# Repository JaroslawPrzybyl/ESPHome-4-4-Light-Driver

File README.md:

# ESPHome-4-4-Light-Driver
**Small light controller with 4 AC SSR outputs and 4 optoisolated inputs, designed for Home Assistant.**

## Design
Not so much to describe - just ESP with power supply and I2C expander, where four ports are used as inputs and four as outputs. Design of inputs and outputs was using by me from a years with other Home Automation systems (old stuff based on AVR CPUs, currently swapping by a bit more modern, HomeAssistant compatible devices), without any problems.  
Outputs are made as SSR relays, switched with zero-cross detection. It means safe switching of any active  load like lamps, etc, but reactive load is not allowed here, so please don't use this device with any induction load, like e.g. engines.   
Inputs are designed for use momentary buttons, each input port responds to shorting it with the COM. Needed wiring of inputs (and outputs) is shown on schematic diagram, with grey lines.  

**WARNING! Don't connect input lines with AC installation or any external power lines, it must be fully separated, only direct connections to switch buttons are allowed**   

## Parts and components
Base of this device is an ESP-07 module, choosen due to possibility to connect external antenna. If it is not needed, can be used also ESP12 or any other with the same footprint, such change has be included in the code.
All other components are listed in BoM file.   

Connection between boards can be done by any method, pins have to be connected 1:1.   
Because reverse connection will damage ESP module, I would recommend to use any connection method, which avoid of it. Connector like  Molex KK would be the best solution, any other with raster 2,54 will be also ok. On my prototype I used ordinary goldpin connector with one pin more than needed, this pin is removed and corresponding pin in the plug is blinded by glue.

PSU: popular chinese HLK-PM01, 5V/0.6A. AC input is protected by varistor and 4A fuse. Due to lack of space I used small fuse SMD 1808 which is not recommended to use with voltage higher than 127V - I know, but I ignored it, because this part really suited me and here important for me was to have something able to make a break in the circuit. Load will be (should be!) active, so there shouldn't be a problems with overvoltage, arcs etc. Fuse is changeable, fuses and sockets were bought on Aliexpress:

https://www.aliexpress.com/item/32840204422.html

Terminal ports - I used old spare, which I had in my draver, but any with raster 5.08mm can be used here. Or - if needed, popular "green" sepparable Phoenix terminal blocks should fit here also.

## Assembly

PCB Gerber files are attached. It is not exactly the same version as shown on photos, it was a prototype, after I did some cosmetic corrections and here I put a final version.  
Both PCBs are prepared for standard DIN rail box case Gainta D3MG http://www.gainta.com/en/d3mg.html, nothing more is needed for assembly, both PCBs fit into the latches inside the case.    
External antena is optional, you can use it or stay with internal - up to you. When device is mounted inside of metal switchbox, external antenna mounted outside of box is strongly recommended.  
Stickers should be printed on self-adhesive paper or foil. In my projects I'm using self-adhesive printable white or silver foil, special for laser printers.   

## Software

From ESP-Home perspective it is really simple device, shouldn't be any problems with the code. The only important thing which should be pointed out is that when you use ESP-07, its integration in ESPHome contains a bug, which is not corrected from the years (was reported many times as I know, without any result). So in declaration of board type, instead of esp_07, has to be used esp01_1m and with this workaround everything works fine.  
Basic proposal of code is added into the files, each input controls its corresponding output, where "short" click on the button just switch on or off the output, "long" click (press and hold more than 1s) switches off all outputs (really useful option for fast switching off the lights in the room). Clicks shorter than 50ms are ignored (debouncing), longer than 5s are also ignored (could be additionally reported as a short circuit on the line, it is not included in this code, but can be simply done).   
Only line 4 works a bit different, here is implemented a timer: short click switches on Out4  for 30 seconds (time value is set as at the top of code), after this time output  will be switched off. Each time it can be switched off manually by click the button again. And long click here works differently: it switches on the output permanently (until switching off by pressing button). 

Exemplary entity works with this code (entity code added into files):

##  

Shield: [![CC BY-NC-SA 4.0][cc-by-nc-sa-shield]][cc-by-nc-sa]

This work is licensed under a
[Creative Commons Attribution-NonCommercial-ShareAlike 4.0 International License][cc-by-nc-sa].

[![CC BY-NC-SA 4.0][cc-by-nc-sa-image]][cc-by-nc-sa]

[cc-by-nc-sa]: http://creativecommons.org/licenses/by-nc-sa/4.0/
[cc-by-nc-sa-image]: https://licensebuttons.net/l/by-nc-sa/4.0/88x31.png
[cc-by-nc-sa-shield]: https://img.shields.io/badge/License-CC%20BY--NC--SA%204.0-lightgrey.svg

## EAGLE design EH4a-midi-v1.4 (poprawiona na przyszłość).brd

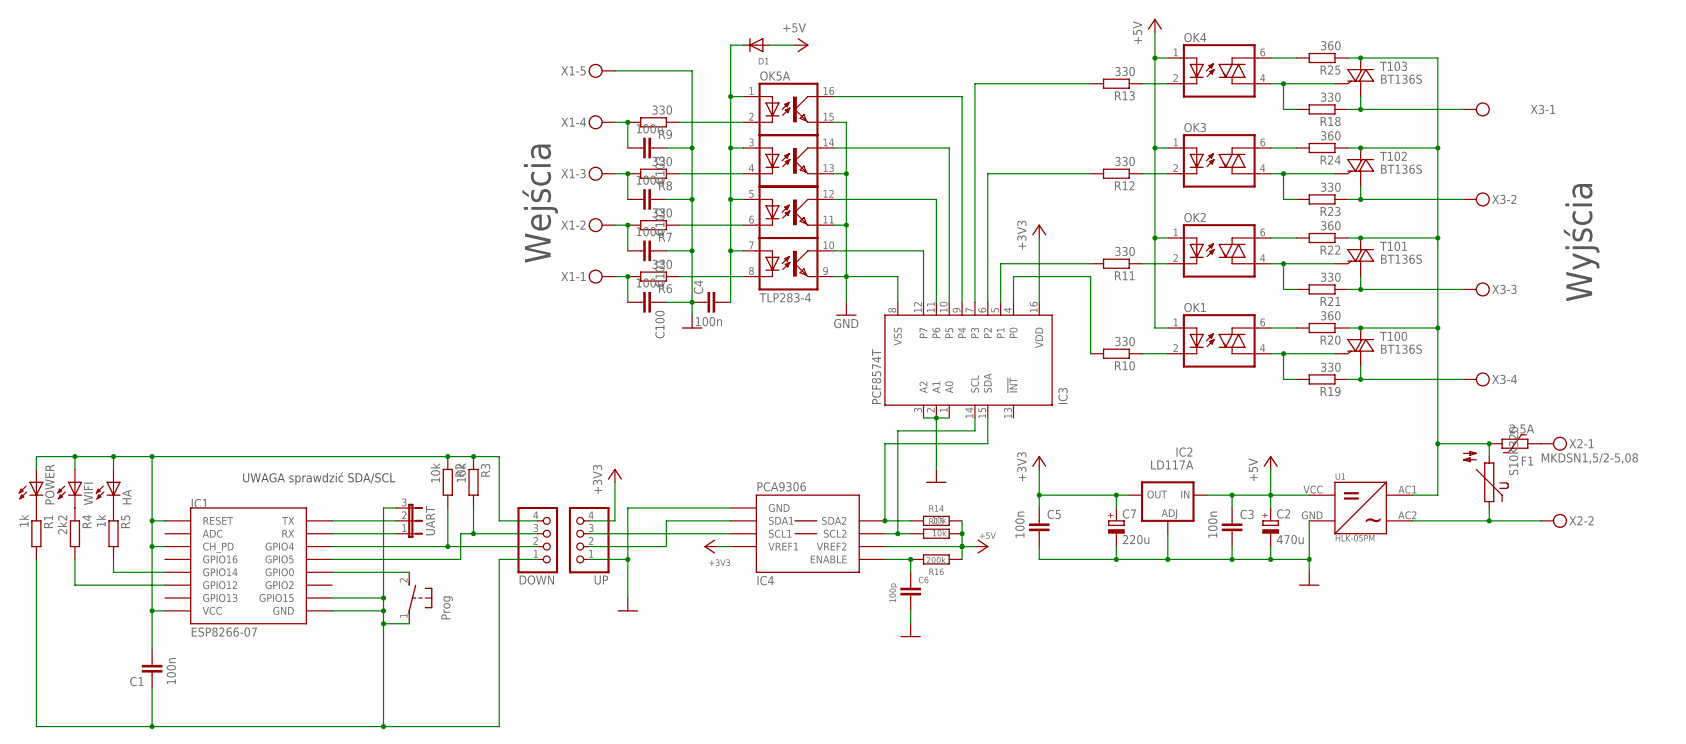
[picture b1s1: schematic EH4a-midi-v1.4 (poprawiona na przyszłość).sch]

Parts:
C1, C3, C4, C5, C100, C101, C102, C103: 100n; C0805
C2: 470u; E3,5-8
C6: 100p; C0805
C7: 220u; E2,5-7
D1: 1N4148; SOD-123
DOWN: PINHD-1X4; 1X04
F1: 2.5A; 2920L
HA: LED3MM
IC1: ESP8266-07; ESP12
IC2: LD117A; SOT223
IC3: PCF8574T; SO16W
IC4: PCA9306; MSOP08
OK1: MOC3043; DIL06
OK2, OK3, OK4: IL420; DIL06
OK5: TLP283-4; MINI-FLAT-16
POWER: LED3MM
R1, R5: 1k; M0805
R2, R3: 10k; M0805
R4: 2k2; M0805
R6, R7, R8, R9, R10, R11, R12, R13: 330; M0805
R14, R15: 10k; R0805
R16: 200k; R0805
R17: S10K320
R18, R19, R21, R23: 330; R1210
R20, R22, R24, R25: 360; R1210
S1: Prog; DTSM-3
T100, T101, T102, T103: BT136S; SOT428
U1: HLK-05PM; HLK-PM01_HLK-PM01
UART: JP2E; JP2
UP: PINHD-1X4; 1X04
WIFI: LED3MM
X1: MKDSN1,5/5-5,08
X2: MKDSN1,5/2-5,08
X3: MKDSN1,5/4-5,08

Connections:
3V3: C1.2, DOWN.4, HA.A, IC1.CH_PD, IC1.RESET, IC1.VCC, POWER.A, R2.1, R3.1, WIFI.A
+3V3: C5.1, C7.+, IC2.2 (OUT), IC2.4 (OUT), IC3.16 (VDD), IC4.2 (VREF1), UP.4
+5V: C2.+, C3.1, D1.A, IC2.3 (IN), IC4.7 (VREF2), OK1.1 (A), OK2.1 (A), OK3.1 (A), OK4.1 (A), R14.1, R15.1, R16.2, U1.VCC
GND: C2.-, C3.2, C4.1, C5.2, C6.2, C7.-, C100.1, C101.1, C102.1, C103.1, IC2.1 (ADJ), IC3.1 (A0), IC3.2 (A1), IC3.3 (A2), IC3.8 (VSS), IC4.1 (GND), OK5.9 (EMIT), OK5.11 (EMIT), OK5.13 (EMIT), OK5.15 (EMIT), U1.GND, UP.1, X1.5
GND1: C1.1, DOWN.1, IC1.GND, IC1.GPIO15, R1.2, S1.1, UART.3
L: F1.1, R17.2, R20.1, R22.1, R24.1, R25.1, T100.MB (LD), T101.MB (LD), T102.MB (LD), T103.MB (LD), U1.AC1
unnamed: IC3.7 (P3), R13.2
unnamed: IC3.10 (P5), OK5.14 (COL)
unnamed: IC3.11 (P6), OK5.12 (COL)
unnamed: IC3.12 (P7), OK5.10 (COL)
unnamed: IC3.6 (P2), R12.2
unnamed: OK4.2 (C), R13.1
unnamed: OK1.2 (C), R10.1
unnamed: OK2.2 (C), R11.1
unnamed: IC3.5 (P1), R11.2
unnamed: IC3.4 (P0), R10.2
unnamed: IC1.GPIO14, R5.2
unnamed: R17.1, U1.AC2, X2.2
unnamed: C103.2, R9.2, X1.4
unnamed: C102.2, R8.2, X1.3
unnamed: F1.2, X2.1
unnamed: POWER.K (C), R1.1
unnamed: R4.1, WIFI.K (C)
unnamed: HA.K (C), R5.1
unnamed: IC1.GPIO12, R4.2
unnamed: IC1.GPIO0, S1.2
unnamed: IC1.RX, UART.1
unnamed: IC1.TX, UART.2
unnamed: C6.1, IC4.8 (ENABLE), R16.1
unnamed: IC3.9 (P4), OK5.16 (COL)
unnamed: OK3.2 (C), R12.1
unnamed: C4.2, D1.C, OK5.1 (A), OK5.3 (A), OK5.5 (A), OK5.7 (A)
unnamed: OK5.2 (C), R9.1
unnamed: OK5.4 (C), R8.1
unnamed: OK5.6 (C), R7.1
unnamed: OK5.8 (C), R6.1
unnamed: OK1.4 (A1), R19.2, T100.3 (G)
unnamed: R19.1, T100.1 (CM), X3.4
unnamed: C101.2, R7.2, X1.2
unnamed: C100.2, R6.2, X1.1
unnamed: OK2.4 (A1), R21.2, T101.3 (G)
unnamed: R21.1, T101.1 (CM), X3.3
unnamed: OK3.4 (A1), R23.2, T102.3 (G)
unnamed: R23.1, T102.1 (CM), X3.2
unnamed: OK4.4 (A1), R18.2, T103.3 (G)
unnamed: R18.1, T103.1 (CM), X3.1
unnamed: OK4.6 (A2), R25.2
unnamed: OK3.6 (A2), R24.2
unnamed: OK2.6 (A2), R22.2
unnamed: OK1.6 (A2), R20.2
SCL: IC3.14 (SCL), IC4.6 (SCL2), R15.2
SCL1: DOWN.3, IC1.GPIO5, R3.2
SCL': IC4.3 (SCL1), UP.3
SDA: IC3.15 (SDA), IC4.5 (SDA2), R14.2
SDA1: DOWN.2, IC1.GPIO4, R2.2
SDA': IC4.4 (SDA1), UP.2

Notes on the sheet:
Wejścia
Wyjścia
UWAGA sprawdzić SDA/SCL

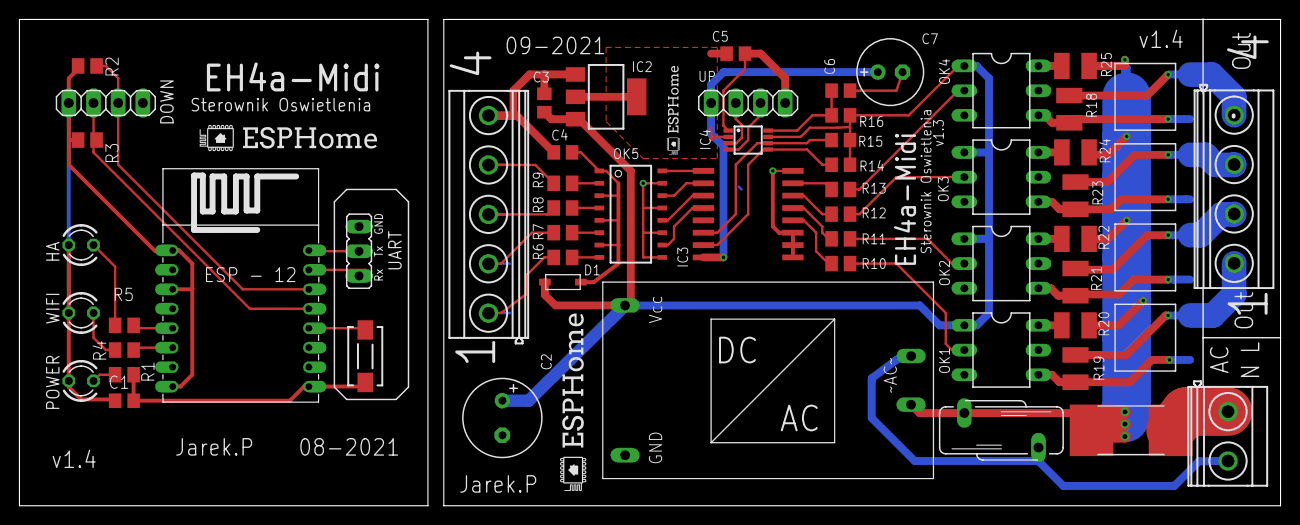
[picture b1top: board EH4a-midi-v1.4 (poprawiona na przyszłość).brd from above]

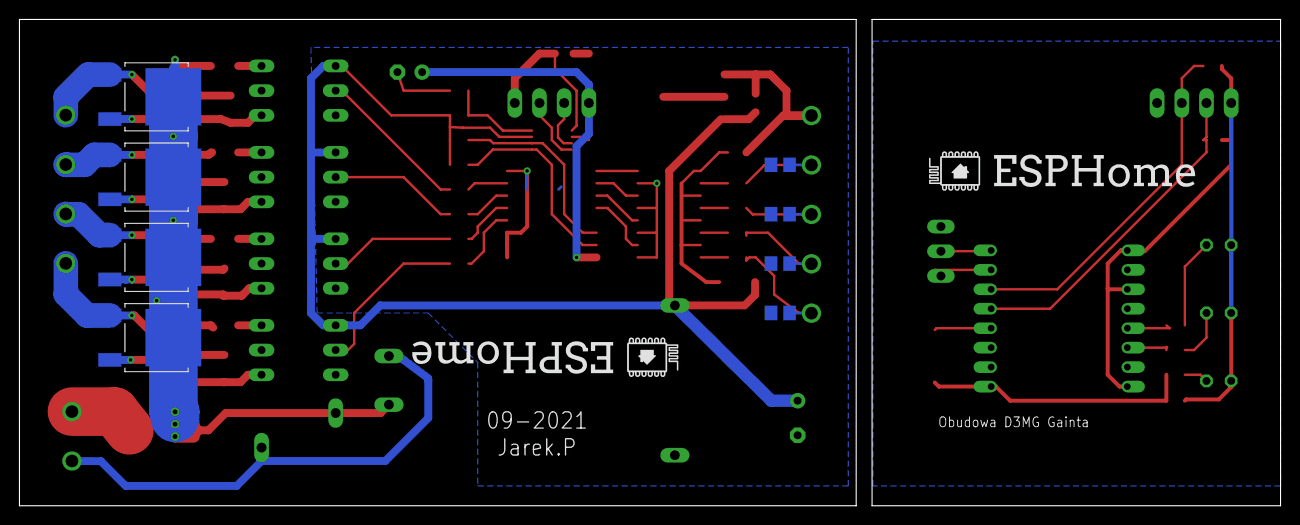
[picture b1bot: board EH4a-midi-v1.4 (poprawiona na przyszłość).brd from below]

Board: 2 copper layers, 129.7 x 50.0 mm, 62 parts (8 on the bottom side), 56 nets.

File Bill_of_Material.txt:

Part    Value   Device               Package            Description
C1      100n    C-EUC0805            C0805
C2      470u    CPOL-EUE3.5-8        E3,5-8
C3      100n    C-EUC0805            C0805
C4      100n    C-EUC0805            C0805
C5      100n    C-EUC0805            C0805
C6      100p    C-EUC0805            C0805
C7      220u    CPOL-EUE2.5-7        E2,5-7
C100    100n    C-EUC0805            C0805
C101    100n    C-EUC0805            C0805
C102    100n    C-EUC0805            C0805
C103    100n    C-EUC0805            C0805
D1      1N5819  DIODESOD-123         SOD-123            Can be any other Shottky.
DOWN            PINHD-1X4            1X04               PIN HEADER
F1      4A      2920L700SL           2920L              SMD1808 fuse socket with fuse 4A
HA              LED3MM               LED3MM             LED 5mm Orange
IC1     ESP8266-ESP-07               ESP12              ESP8266 Wifi module
IC2     LD117A  LD117AS12TR          SOT223
IC3     PCF8574TPCF8574T             SO16W
IC4     PCA9306 IC2_LEVEL_TRANSLATER MSOP08
OK1     MOC3041 IL420                DIL06
OK2     MOC3041 IL420                DIL06
OK3     MOC3041 IL420                DIL06
OK4     MOC3041 IL420                DIL06
OK5     TLP283-4TLP283-4             MINI-FLAT-16
POWER           LED3MM               LED3MM             LED 5mm Green
R1      820     R-EU_M0805           M0805
R2      10k     R-EU_M0805           M0805
R3      10k     R-EU_M0805           M0805
R4      3k3     R-EU_M0805           M0805
R5      820     R-EU_M0805           M0805
R6      330     R-EU_M0805           M0805
R7      330     R-EU_M0805           M0805
R8      330     R-EU_M0805           M0805
R9      330     R-EU_M0805           M0805
R10     330     R-EU_M0805           M0805
R11     330     R-EU_M0805           M0805
R12     330     R-EU_M0805           M0805
R13     330     R-EU_M0805           M0805
R14     10k     R-EU_R0805           R0805
R15     10k     R-EU_R0805           R0805
R16     200k    R-EU_R0805           R0805
R17     S10K300 S10K300              S10K300            VARISTOR
R18     330     R-EU_R1210           R1210
R19     330     R-EU_R1210           R1210
R20     360     R-EU_R1210           R1210
R21     330     R-EU_R1210           R1210
R22     360     R-EU_R1210           R1210
R23     330     R-EU_R1210           R1210
R24     360     R-EU_R1210           R1210
R25     360     R-EU_R1210           R1210
S1      Prog    DTSM-3               DTSM-3				SMD mountable tact switch
T100    BT136S  ACT108WDPAK          SOT428
T101    BT136S  ACT108WDPAK          SOT428
T102    BT136S  ACT108WDPAK          SOT428
T103    BT136S  ACT108WDPAK          SOT428
U1      HLK-05PMHLK-PM01_HLK-PM01    HLK-PM01_HLK-PM01  HLK-PM05
UART            JP2E                 JP2                JUMPER
UP              PINHD-1X4            1X04               PIN HEADER
WIFI            LED3MM               LED3MM             LED 5mm Blue
X1      MKDSN1,5MKDSN1,5/5-5,08      MKDSN1,5/5-5,08
X2      230V AC MKDSN1,5/2-5,08      MKDSN1,5/2-5,08
X3      MKDSN1,5MKDSN1,5/4-5,08      MKDSN1,5/4-5,08

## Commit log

2021-11-09 Rename EH4a-midi-v1.4 BOM.txt to Bill_of_Material.txt
